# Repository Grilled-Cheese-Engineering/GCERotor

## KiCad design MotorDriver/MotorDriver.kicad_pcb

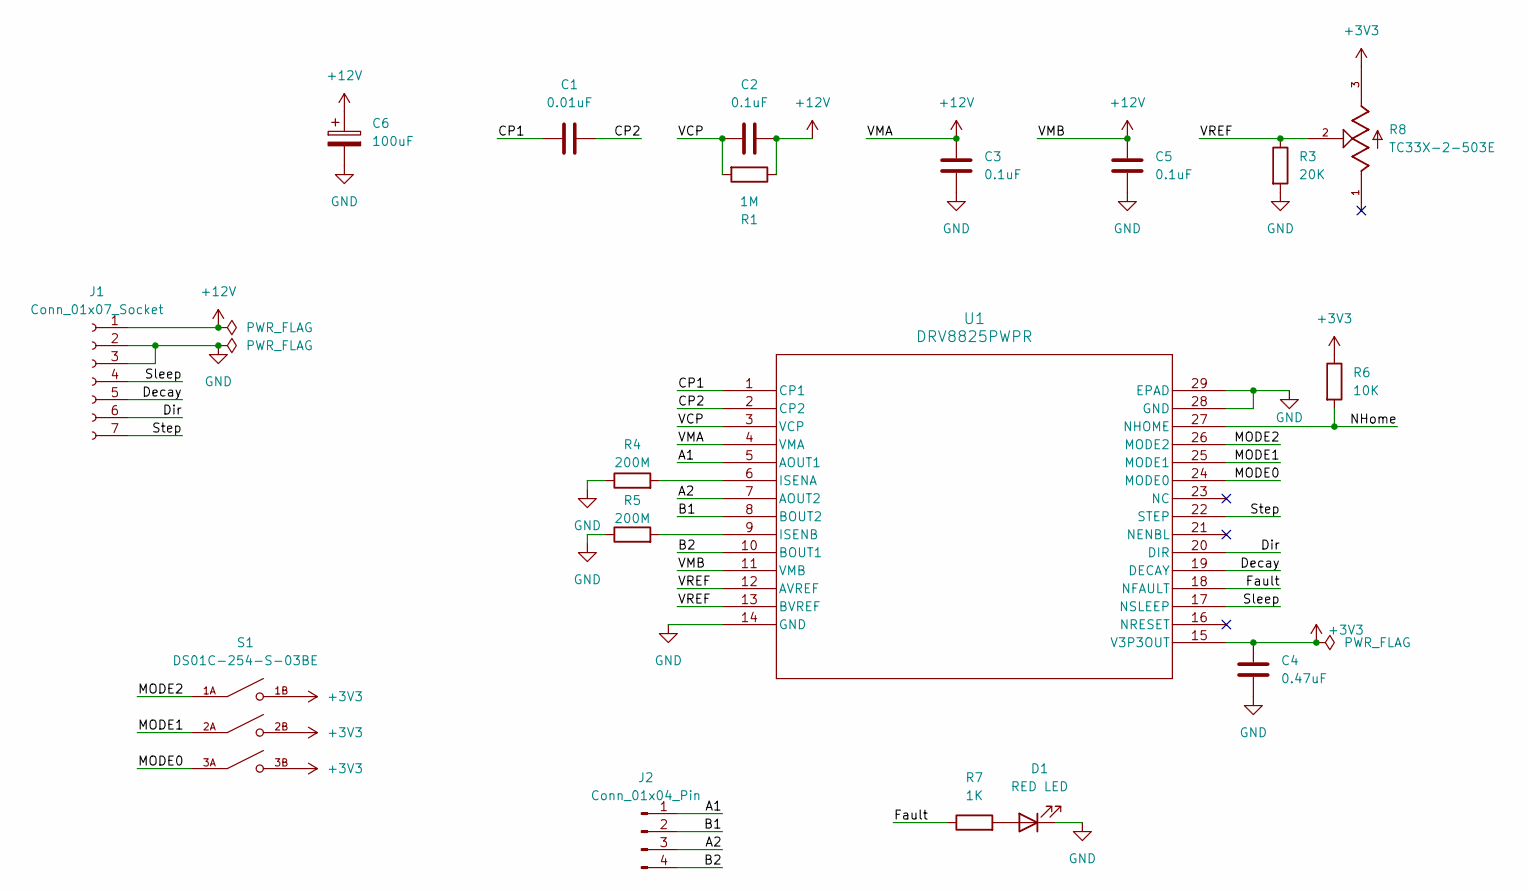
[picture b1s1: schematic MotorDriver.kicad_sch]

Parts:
C1: 0.01uF; C_1206_3216Metric
C2, C3, C5: 0.1uF; C_1206_3216Metric
C4: 0.47uF; C_1206_3216Metric
C6: 100uF; CP_Radial_D6.3mm_P2.50mm
D1: RED LED; LED_1206_3216Metric
J1: Conn_01x07_Socket; PinSocket_1x07_P2.54mm_Vertical
J2: Conn_01x04_Pin; PinHeader_1x04_P2.54mm_Vertical
R1: 1M; R_1206_3216Metric
R3: 20K; R_1206_3216Metric
R4, R5: 200M; R_1206_3216Metric
R6: 10K; R_1206_3216Metric
R7: 1K; R_1206_3216Metric
R8: TC33X-2-503E; TRIM_TC33X-2-503E
S1: DS01C-254-S-03BE; SW_DS01C-254-S-03BE; PARTREV 1.0
U1: DRV8825PWPR; PWP28_5P18X3P1

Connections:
+3V3: C4.2, R6.1, R8.3, S1.1B, S1.2B, S1.3B, U1.15 (V3P3OUT)
+12V: C2.2, C3.2, C5.2, C6.1, J1.1, R1.1, U1.4 (VMA), U1.11 (VMB)
/A1: J2.1, U1.5 (AOUT1)
/A2: J2.3, U1.7 (AOUT2)
/B1: J2.2, U1.8 (BOUT2)
/B2: J2.4, U1.10 (BOUT1)
/CP1: C1.1, U1.1 (CP1)
/CP2: C1.2, U1.2 (CP2)
/Decay: J1.5, U1.19 (DECAY)
/Dir: J1.6, U1.20 (DIR)
/Fault: R7.1, U1.18 (NFAULT)
/MODE0: S1.3A, U1.24 (MODE0)
/MODE1: S1.2A, U1.25 (MODE1)
/MODE2: S1.1A, U1.26 (MODE2)
/NHome: R6.2, U1.27 (NHOME)
/Sleep: J1.4, U1.17 (NSLEEP)
/Step: J1.7, U1.22 (STEP)
/VCP: C2.1, R1.2, U1.3 (VCP)
/VREF: R3.1, R8.2, U1.12 (AVREF), U1.13 (BVREF)
GND: C3.1, C4.1, C5.1, C6.2, D1.1 (K), J1.2, J1.3, R3.2, R4.1, R5.1, U1.14 (GND), U1.28 (GND), U1.29 (EPAD)
unnamed: D1.2 (A), R7.2
unnamed: R4.2, U1.6 (ISENA)
unnamed: R5.2, U1.9 (ISENB)

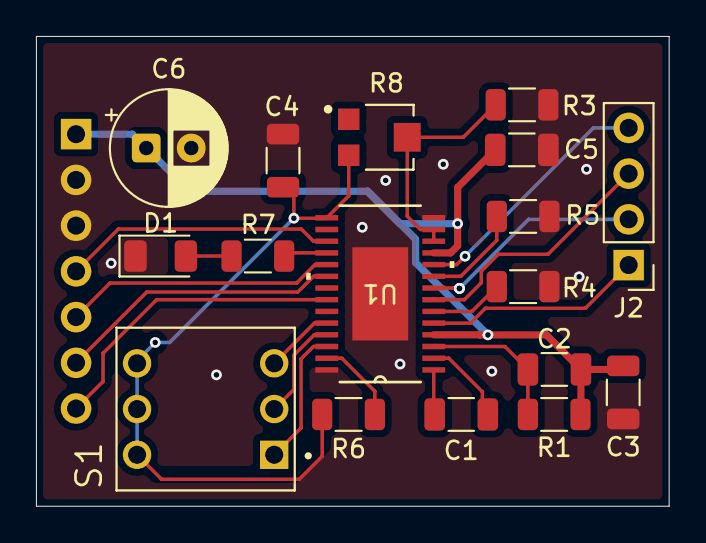
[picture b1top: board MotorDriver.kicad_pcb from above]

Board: 2 copper layers, 35.2 x 26.1 mm, 18 parts (1 on the bottom side), 23 nets.
